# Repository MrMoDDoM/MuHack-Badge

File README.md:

# MuHack-Badge
Official repository for MuHack Badge.

The board features an RP2040 as main microcontroller running micropython.
Its job is to setup and stream data from the Bosh Sensor Hub BHI106B, as well as controlling the LEDs.

```Hardware/``` folder contains the KiCad project

```Software/``` folder contains the BOSS system and the sketch for the ESP32

TODOs:
 - [ ] Connect the interrupt line of BHI to the RP2040
 - [ ] Invert TX/RX of UART between ESP32 and RP2040
 - [ ] Change to a bigger footprint of ESP32 debug port
 - [ ] Maybe add two button for boot sel and reset for the ESP32
 - [ ] Change button battery footprint
 - [ ] Improve silkscreen text size
 - [ ] Add silkscreen label for many things (pinout, battery polarity, etc)
 - [ ] Expose BHI's internal I2C and interrupt line (for future sensors)
 - [ ] Move I2C pull-up resistor
 - [ ] Add led polarity
 - [ ] Remove power inductor (or change to an available one)
 - [ ] Maybe add a way to switch LEDs data line to the ESP32 instead of the RP2040
 - [ ] Docs and code comments
 - [ ] Remove the D16 Schottky Diode from the battery line
 
 Special Thanks to:
 @gcammisa and Paolino

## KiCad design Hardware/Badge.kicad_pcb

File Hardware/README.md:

# MuHack-Badge
Official repository for MuHack Badge

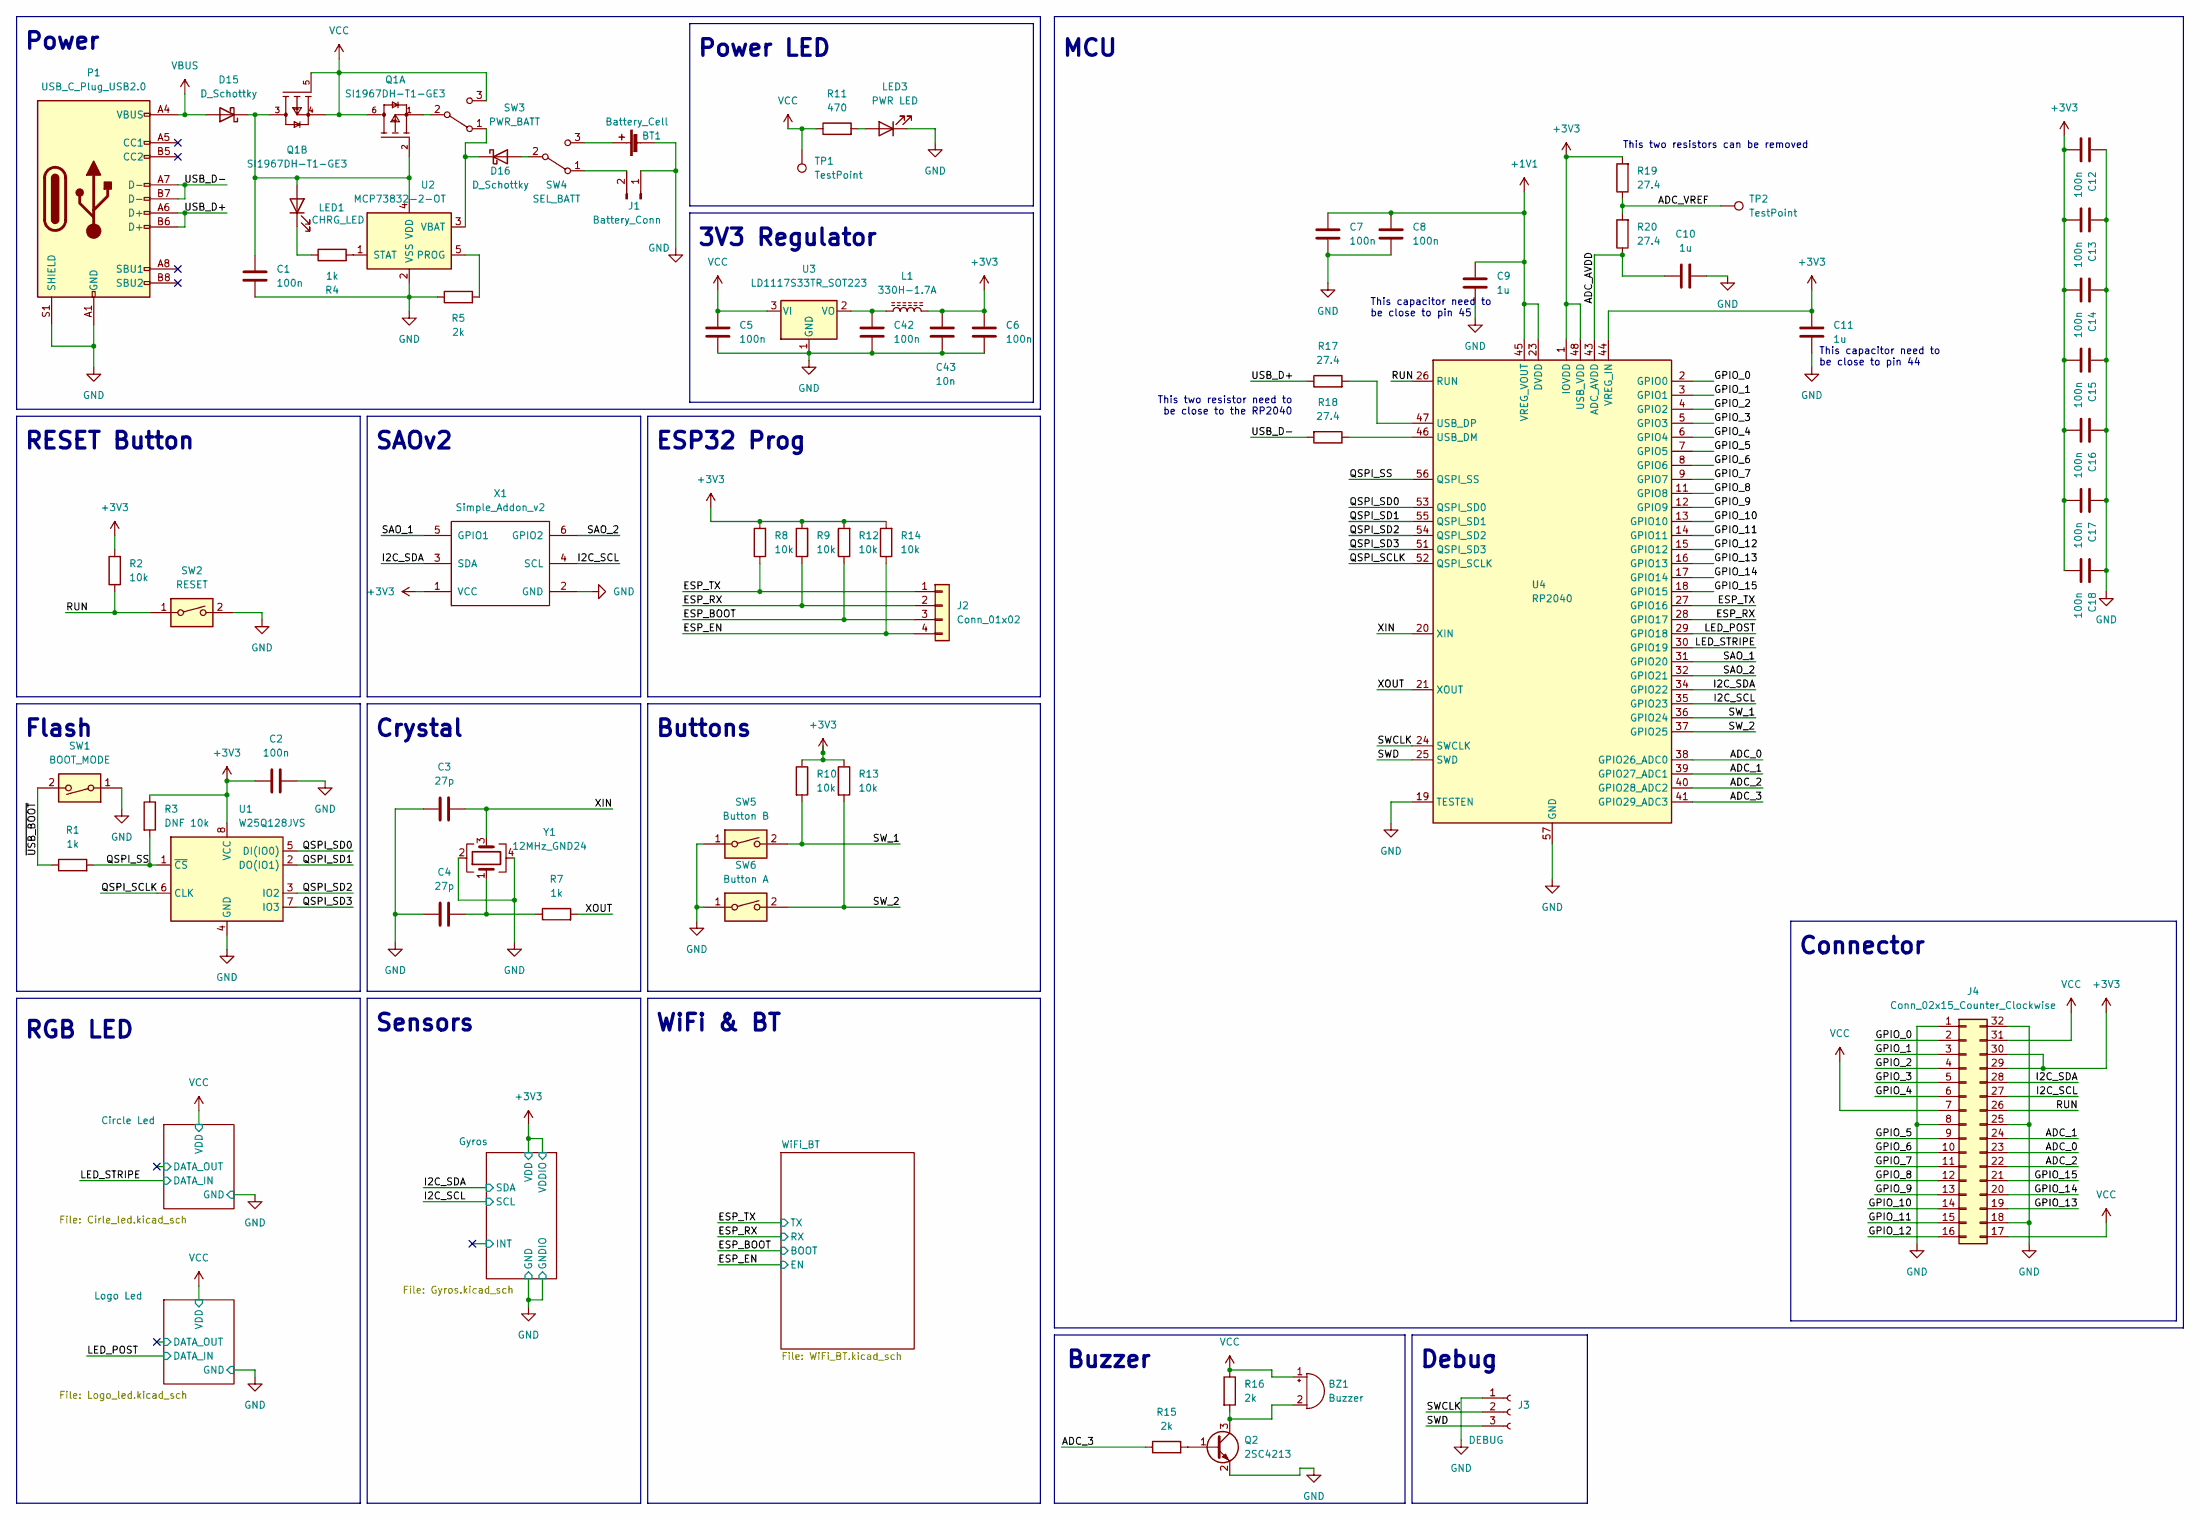
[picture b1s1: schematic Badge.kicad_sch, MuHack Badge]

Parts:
BT1: Battery_Cell; BatteryHolder_LINX_BAT-HLD-012-SMT
BZ1: Buzzer; Buzzer_Mallory_AST1109MLTRQ
C1, C2, C5, C6, C7, C8, C12, C13, C14, C15, C16, C17, C18, C42: 100n; C_0402_1005Metric
C3, C4: 27p; C_0402_1005Metric
C9, C10, C11: 1u; C_0402_1005Metric
C43: 10n; C_0402_1005Metric
D15, D16: D_Schottky; D_SMA
J1: Battery_Conn; JST_PH_B2B-PH-K_1x02_P2.00mm_Vertical
J2: Conn_01x02; PinSocket_1x04_P1.00mm_Vertical
J3: DEBUG; PinSocket_1x03_P2.54mm_Vertical
J4: Conn_02x15_Counter_Clockwise; PinSocket_2x16_P2.54mm_Vertical
L1: 330H-1.7A; L_0603_1608Metric
LED1: CHRG_LED; LED_0603_1608Metric
LED3: PWR LED; LED_0603_1608Metric
P1: USB_C_Plug_USB2.0; USB_C_Receptacle_Palconn_UTC16-G
Q1: SI1967DH-T1-GE3; Vishay-S-03946-07_2001-B-0; mouser part number 781-SI1967DH-T1-GE3; digikey description MOSFET 2P-CH 20V 1.3A SC70-6
Q2: 2SC4213; SOT-323_SC-70
R1, R4, R7: 1k; R_0402_1005Metric
R2, R8, R9, R10, R12, R13, R14: 10k; R_0402_1005Metric
R3: DNF 10k; R_0402_1005Metric
R5, R15, R16: 2k; R_0402_1005Metric
R11: 470; R_0402_1005Metric
R17, R18, R19, R20: 27.4; R_0402_1005Metric
SW1: BOOT_MODE; TS-1187A-B-A-B
SW2: RESET; TS-1187A-B-A-B
SW3: PWR_BATT; SW_SPDT_CK-JS102011SAQN
SW4: SEL_BATT; SW_SPDT_CK-JS102011SAQN
SW5: Button B; TS-1187A-B-A-B
SW6: Button A; TS-1187A-B-A-B
TP1, TP2: TestPoint; TestPoint_Pad_D1.0mm
U1: W25Q128JVS; SOIC-8_5.23x5.23mm_P1.27mm
U2: MCP73832-2-OT; SOT-23-5
U3: LD1117S33TR_SOT223; SOT-223-3_TabPin2
U4: RP2040; QFN-56-1EP_7x7mm_P0.4mm_EP3.2x3.2mm
X1: Simple_Addon_v2; Simple_Addon_v2-BADGE-2x3
Y1: 12MHz_GND24; Crystal_SMD_3225-4Pin_3.2x2.5mm

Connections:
+1V1: C7.1, C8.1, C9.2, U4.23 (DVDD), U4.45 (VREG_VOUT), U4.50 (DVDD)
+3V3: C2.1, C6.2, C11.1, C12.2, C13.2, C14.2, C15.2, C16.2, C17.2, C18.2, C43.2, J4.29, J4.30, L1.2, R2.2, R3.1, R8.2, R9.2, R10.1, R12.2, R13.1, R14.2, R19.2, U1.8 (VCC), U4.1 (IOVDD), U4.10 (IOVDD), U4.22 (IOVDD), U4.33 (IOVDD), U4.42 (IOVDD), U4.44 (VREG_IN), U4.48 (USB_VDD), U4.49 (IOVDD), X1.1 (VCC); also elsewhere on the board
/ADC_0: J4.23, U4.38 (GPIO26_ADC0)
/ADC_1: J4.24, U4.39 (GPIO27_ADC1)
/ADC_2: J4.22, U4.40 (GPIO28_ADC2)
/ADC_3: R15.1, U4.41 (GPIO29_ADC3)
/ADC_AVDD: C10.1, R20.1, U4.43 (ADC_AVDD)
/ADC_VREF: R19.1, R20.2, TP2.1
/ESP_BOOT: J2.3, R12.1; also elsewhere on the board
/ESP_EN: J2.4, R14.1; also elsewhere on the board
/ESP_RX: J2.2, R9.1, U4.28 (GPIO17); also elsewhere on the board
/ESP_TX: J2.1, R8.1, U4.27 (GPIO16); also elsewhere on the board
/GPIO_0: J4.2, U4.2 (GPIO0)
/GPIO_1: J4.3, U4.3 (GPIO1)
/GPIO_2: J4.4, U4.4 (GPIO2)
/GPIO_3: J4.5, U4.5 (GPIO3)
/GPIO_4: J4.6, U4.6 (GPIO4)
/GPIO_5: J4.9, U4.7 (GPIO5)
/GPIO_6: J4.10, U4.8 (GPIO6)
/GPIO_7: J4.11, U4.9 (GPIO7)
/GPIO_8: J4.12, U4.11 (GPIO8)
/GPIO_9: J4.13, U4.12 (GPIO9)
/GPIO_10: J4.14, U4.13 (GPIO10)
/GPIO_11: J4.15, U4.14 (GPIO11)
/GPIO_12: J4.16, U4.15 (GPIO12)
/GPIO_13: J4.19, U4.16 (GPIO13)
/GPIO_14: J4.20, U4.17 (GPIO14)
/GPIO_15: J4.21, U4.18 (GPIO15)
/I2C_SCL: J4.27, U4.35 (GPIO23), X1.4 (SCL); also elsewhere on the board
/I2C_SDA: J4.28, U4.34 (GPIO22), X1.3 (SDA); also elsewhere on the board
/LED_POST: U4.29 (GPIO18); also elsewhere on the board
/LED_STRIPE: U4.30 (GPIO19); also elsewhere on the board
/QSPI_SCLK: U1.6 (CLK), U4.52 (QSPI_SCLK)
/QSPI_SD0: U1.5 (DI(IO0)), U4.53 (QSPI_SD0)
/QSPI_SD1: U1.2 (DO(IO1)), U4.55 (QSPI_SD1)
/QSPI_SD2: U1.3 (IO2), U4.54 (QSPI_SD2)
/QSPI_SD3: U1.7 (IO3), U4.51 (QSPI_SD3)
/QSPI_SS: R1.2, R3.2, U1.1 (~CS), U4.56 (QSPI_SS)
/RUN: J4.26, R2.1, SW2.1, U4.26 (RUN)
/SAO_1: U4.31 (GPIO20), X1.5 (GPIO1)
/SAO_2: U4.32 (GPIO21), X1.6 (GPIO2)
/SWCLK: J3.2, U4.24 (SWCLK)
/SWD: J3.3, U4.25 (SWD)
/SW_1: R10.2, SW5.2, U4.36 (GPIO24)
/SW_2: R13.2, SW6.2, U4.37 (GPIO25)
/USB_D+: P1.A6 (D+), P1.B6 (D+), R17.1
/USB_D-: P1.A7 (D-), P1.B7 (D-), R18.2
/XIN: C3.2, U4.20 (XIN), Y1.3
/XOUT: R7.2, U4.21 (XOUT)
/~USB_BOOT: R1.1, SW1.2
GND: BT1.2 (-), C1.2, C2.2, C3.1, C4.1, C5.1, C6.1, C7.2, C8.2, C9.1, C10.2, C11.2, C12.1, C13.1, C14.1, C15.1, C16.1, C17.1, C18.1, C42.1, C43.1, J1.1, J3.1, J4.1, J4.8, J4.18, J4.25, J4.32, LED3.1 (K), P1.A1 (GND), P1.A12 (GND), P1.B1 (GND), P1.B12 (GND), P1.S1 (SHIELD), Q2.2 (E), R5.1, SW1.1, SW2.2, SW5.1, SW6.1, U1.4 (GND), U2.2 (VSS), U3.1 (GND), U4.19 (TESTEN), U4.57 (GND), X1.2 (GND), Y1.2, Y1.4; also elsewhere on the board
unnamed: BT1.1 (+), SW4.3 (C)
unnamed: BZ1.2 (+), Q2.3 (C), R16.2
unnamed: C1.1, D15.1 (K), LED1.2 (A), Q1.2 (G1), Q1.3 (D2), U2.4 (VDD)
unnamed: C4.2, R7.1, Y1.1
unnamed: C42.2, L1.1, U3.2 (VO)
unnamed: D16.1 (K), SW3.1 (A), U2.3 (VBAT)
unnamed: D16.2 (A), SW4.2 (B)
unnamed: J1.2, SW4.1 (A)
unnamed: LED1.1 (K), R4.1
unnamed: LED3.2 (A), R11.2
unnamed: Q1.1 (S1), SW3.2 (B)
unnamed: Q2.1 (B), R15.2
unnamed: R4.2, U2.1 (STAT)
unnamed: R5.2, U2.5 (PROG)
unnamed: R17.2, U4.47 (USB_DP)
unnamed: R18.1, U4.46 (USB_DM)
VBUS: D15.2 (A), P1.A4 (VBUS), P1.A9 (VBUS), P1.B4 (VBUS), P1.B9 (VBUS)
VCC: BZ1.1 (-), C5.2, J4.7, J4.17, J4.31, Q1.4 (S2), Q1.5 (G2), Q1.6 (D1), R11.1, R16.1, SW3.3 (C), TP1.1, U3.3 (VI); also elsewhere on the board

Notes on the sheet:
This capacitor need to be close to pin 44
Buttons
Power
This two resistor need to be close to the RP2040
ESP32 Prog
3V3 Regulator
Crystal
Power LED
This capacitor need to be close to pin 45
RESET Button
This two resistors can be removed
WiFi & BT
Connector
SAOv2
Buzzer
Flash
Debug
Sensors
MCU
RGB LED

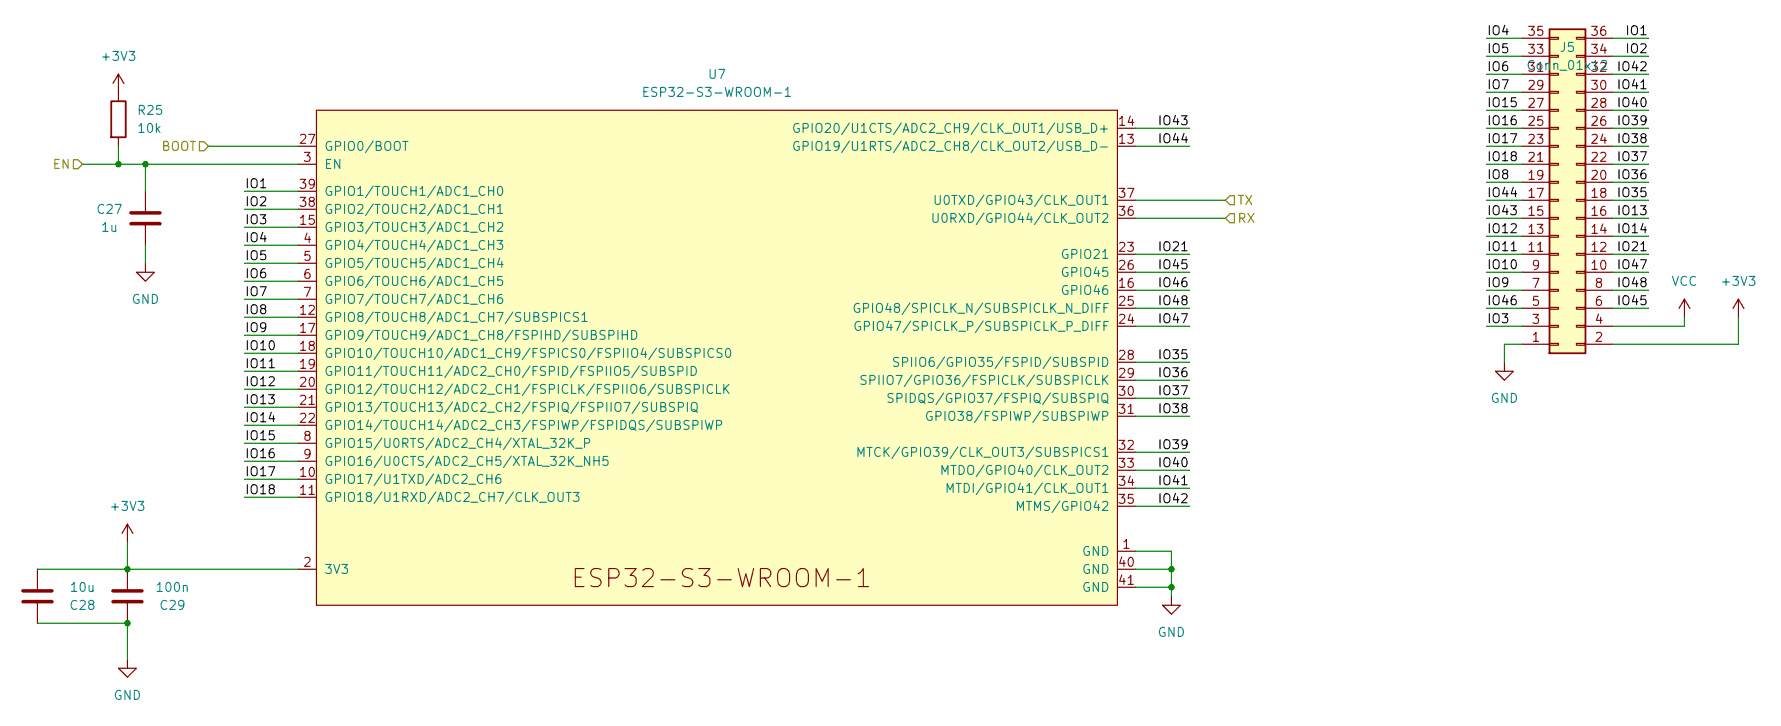
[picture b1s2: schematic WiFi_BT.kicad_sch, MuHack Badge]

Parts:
C27: 1u; C_0402_1005Metric
C28: 10u; C_0402_1005Metric
C29: 100n; C_0402_1005Metric
J5: Conn_01x12; PinSocket_2x18_P1.27mm_Vertical
R25: 10k; R_0402_1005Metric
U7: ESP32-S3-WROOM-1

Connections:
+3V3: C28.1, C29.1, J5.2, R25.1, U7.2 (3V3); also elsewhere on the board
/ESP_BOOT: U7.27 (GPIO0/BOOT); also elsewhere on the board
/ESP_EN: C27.2, R25.2, U7.3 (EN); also elsewhere on the board
/ESP_RX: U7.36 (U0RXD/GPIO44/CLK_OUT2); also elsewhere on the board
/ESP_TX: U7.37 (U0TXD/GPIO43/CLK_OUT1); also elsewhere on the board
/WiFi_BT/IO1: J5.36, U7.39 (GPIO1/TOUCH1/ADC1_CH0)
/WiFi_BT/IO2: J5.34, U7.38 (GPIO2/TOUCH2/ADC1_CH1)
/WiFi_BT/IO3: J5.3, U7.15 (GPIO3/TOUCH3/ADC1_CH2)
/WiFi_BT/IO4: J5.35, U7.4 (GPIO4/TOUCH4/ADC1_CH3)
/WiFi_BT/IO5: J5.33, U7.5 (GPIO5/TOUCH5/ADC1_CH4)
/WiFi_BT/IO6: J5.31, U7.6 (GPIO6/TOUCH6/ADC1_CH5)
/WiFi_BT/IO7: J5.29, U7.7 (GPIO7/TOUCH7/ADC1_CH6)
/WiFi_BT/IO8: J5.19, U7.12 (GPIO8/TOUCH8/ADC1_CH7/SUBSPICS1)
/WiFi_BT/IO9: J5.7, U7.17 (GPIO9/TOUCH9/ADC1_CH8/FSPIHD/SUBSPIHD)
/WiFi_BT/IO10: J5.9, U7.18 (GPIO10/TOUCH10/ADC1_CH9/FSPICS0/FSPIIO4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)
/WiFi_BT/IO11: J5.11, U7.19 (GPIO11/TOUCH11/ADC2_CH0/FSPID/FSPIIO5/S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)
/WiFi_BT/IO12: J5.13, U7.20 (GPIO12/TOUCH12/ADC2_CH1/FSPICLK/FSPIIO6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)
/WiFi_BT/IO13: J5.16, U7.21 (GPIO13/TOUCH13/ADC2_CH2/FSPIQ/FSPIIO7/S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)
/WiFi_BT/IO14: J5.14, U7.22 (GPIO14/TOUCH14/ADC2_CH3/FSPIWP/FSPIDQS/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)
/WiFi_BT/IO15: J5.27, U7.8 (GPIO15/U0RTS/ADC2_CH4/XTAL_32K_P)
/WiFi_BT/IO16: J5.25, U7.9 (GPIO16/U0CTS/ADC2_CH5/XTAL_32K_NH5)
/WiFi_BT/IO17: J5.23, U7.10 (GPIO17/U1TXD/ADC2_CH6)
/WiFi_BT/IO18: J5.21, U7.11 (GPIO18/U1RXD/ADC2_CH7/CLK_OUT3)
/WiFi_BT/IO21: J5.12, U7.23 (GPIO21)
/WiFi_BT/IO35: J5.18, U7.28 (SPIIO6/GPIO35/FSPID/SUBSPID)
/WiFi_BT/IO36: J5.20, U7.29 (SPIIO7/GPIO36/FSPICLK/SUBSPICLK)
/WiFi_BT/IO37: J5.22, U7.30 (SPIDQS/GPIO37/FSPIQ/SUBSPIQ)
/WiFi_BT/IO38: J5.24, U7.31 (GPIO38/FSPIWP/SUBSPIWP)
/WiFi_BT/IO39: J5.26, U7.32 (MTCK/GPIO39/CLK_OUT3/SUBSPICS1)
/WiFi_BT/IO40: J5.28, U7.33 (MTDO/GPIO40/CLK_OUT2)
/WiFi_BT/IO41: J5.30, U7.34 (MTDI/GPIO41/CLK_OUT1)
/WiFi_BT/IO42: J5.32, U7.35 (MTMS/GPIO42)
/WiFi_BT/IO43: J5.15, U7.14 (GPIO20/U1CTS/ADC2_CH9/CLK_OUT1/USB_D+)
/WiFi_BT/IO44: J5.17, U7.13 (GPIO19/U1RTS/ADC2_CH8/CLK_OUT2/USB_D-)
/WiFi_BT/IO45: J5.6, U7.26 (GPIO45)
/WiFi_BT/IO46: J5.5, U7.16 (GPIO46)
/WiFi_BT/IO47: J5.10, U7.24 (GPIO47/SPICLK_P/SUBSPICLK_P_DIFF)
/WiFi_BT/IO48: J5.8, U7.25 (GPIO48/SPICLK_N/SUBSPICLK_N_DIFF)
GND: C27.1, C28.2, C29.2, J5.1, U7.1 (GND), U7.40 (GND), U7.41 (GND); also elsewhere on the board
VCC: J5.4; also elsewhere on the board

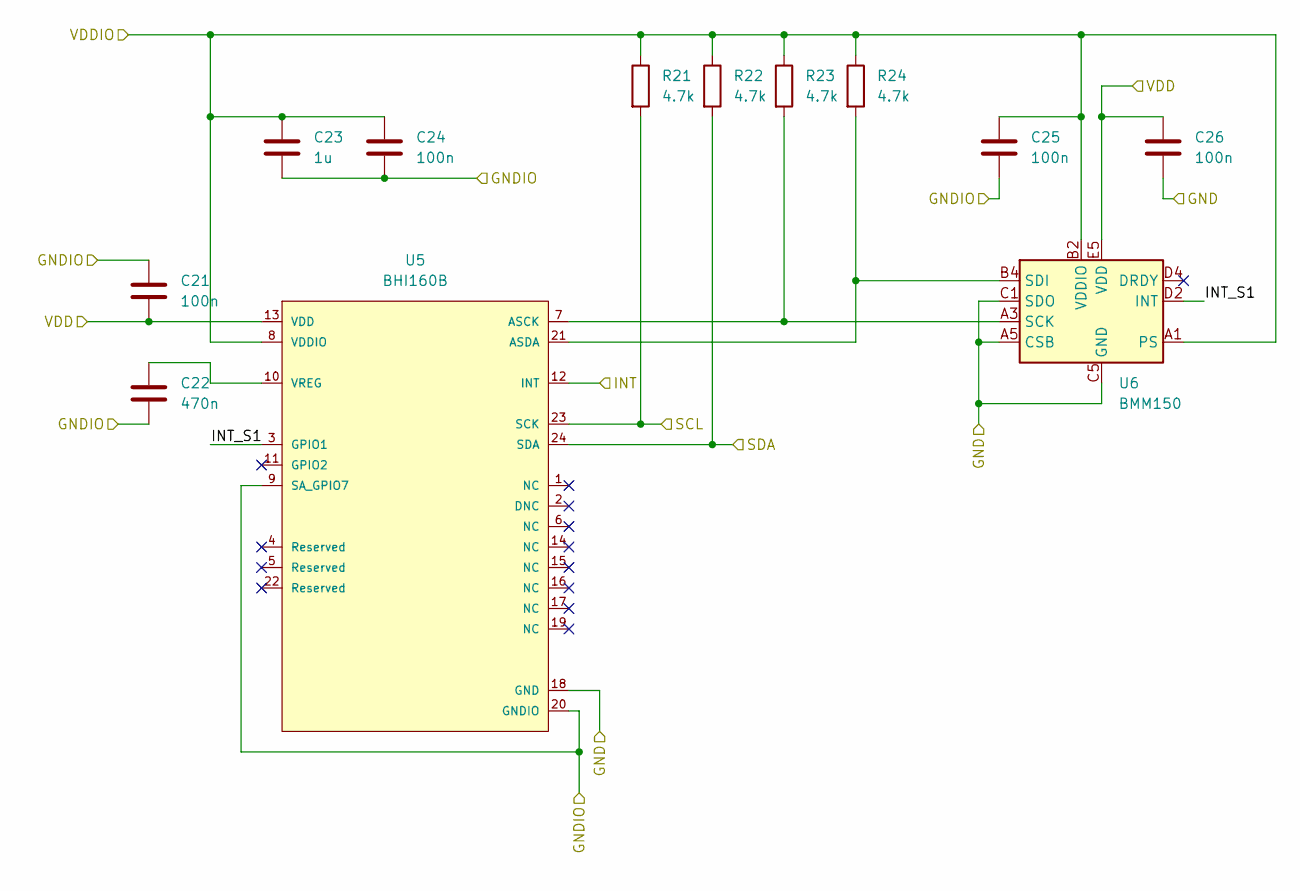
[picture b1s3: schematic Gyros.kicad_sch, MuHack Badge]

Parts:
C21, C24, C25, C26: 100n; C_0402_1005Metric
C22: 470n; C_0402_1005Metric
C23: 1u; C_0402_1005Metric
R21, R22, R23, R24: 4.7k; R_0402_1005Metric
U5: BHI160B; Bosch_Sensortec-BHI160B-MFG; mouser part number 262-BHI160B; digikey description IMU ACCEL/GYRO 3-AXIS I2C 24LGA
U6: BMM150; Bosch_Sensortec-BMM150-IPC_B

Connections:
+3V3: C21.2, C23.1, C24.1, C25.2, C26.2, R21.1, R22.1, R23.1, R24.1, U5.8 (VDDIO), U5.13 (VDD), U6.A1 (PS), U6.B2 (VDDIO), U6.E5 (VDD); also elsewhere on the board
/Gyros/INT: U5.12 (INT)
/Gyros/INT_S1: U5.3 (GPIO1), U6.D2 (INT)
/I2C_SCL: R21.2, U5.23 (SCK); also elsewhere on the board
/I2C_SDA: R22.2, U5.24 (SDA); also elsewhere on the board
GND: C21.1, C22.2, C23.2, C24.2, C25.1, C26.1, U5.9 (SA_GPIO7), U5.18 (GND), U5.20 (GNDIO), U6.A5 (CSB), U6.C1 (SDO), U6.C5 (GND), U6.E1 (GND), U6.E3 (GND); also elsewhere on the board
unnamed: C22.1, U5.10 (VREG)
unnamed: R23.2, U5.7 (ASCK), U6.A3 (SCK)
unnamed: R24.2, U5.21 (ASDA), U6.B4 (SDI)

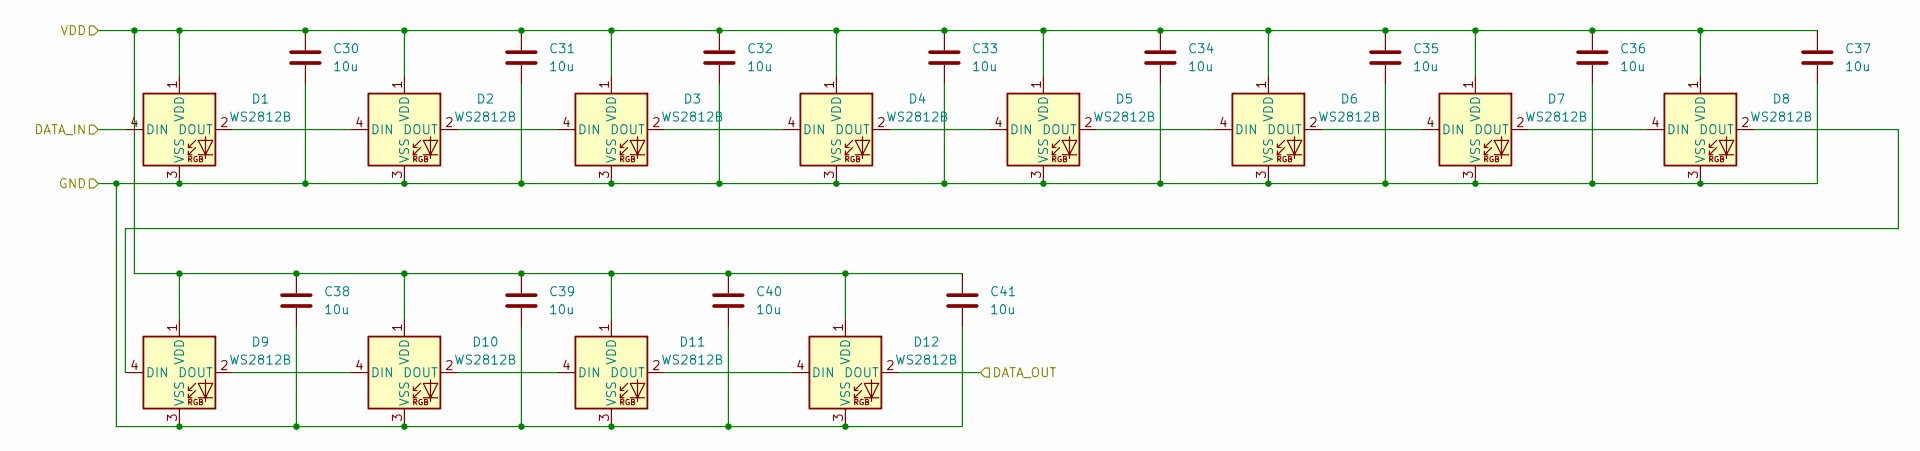
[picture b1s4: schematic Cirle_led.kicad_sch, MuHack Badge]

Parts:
C30, C31, C32, C33, C34, C35, C36, C37, C38, C39, C40, C41: 10u; C_0402_1005Metric
D1, D2, D3, D4, D5, D6, D7, D8, D9, D10, D11, D12: WS2812B; LED_WS2812B_PLCC4_5.0x5.0mm_P3.2mm

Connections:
/Circle Led/DATA_OUT: D12.2 (DOUT)
/LED_STRIPE: D1.4 (DIN); also elsewhere on the board
GND: C30.2, C31.2, C32.2, C33.2, C34.2, C35.2, C36.2, C37.2, C38.2, C39.2, C40.2, C41.2, D1.3 (VSS), D2.3 (VSS), D3.3 (VSS), D4.3 (VSS), D5.3 (VSS), D6.3 (VSS), D7.3 (VSS), D8.3 (VSS), D9.3 (VSS), D10.3 (VSS), D11.3 (VSS), D12.3 (VSS); also elsewhere on the board
unnamed: D1.2 (DOUT), D2.4 (DIN)
unnamed: D2.2 (DOUT), D3.4 (DIN)
unnamed: D3.2 (DOUT), D4.4 (DIN)
unnamed: D4.2 (DOUT), D5.4 (DIN)
unnamed: D5.2 (DOUT), D6.4 (DIN)
unnamed: D6.2 (DOUT), D7.4 (DIN)
unnamed: D7.2 (DOUT), D8.4 (DIN)
unnamed: D8.2 (DOUT), D9.4 (DIN)
unnamed: D10.2 (DOUT), D11.4 (DIN)
unnamed: D9.2 (DOUT), D10.4 (DIN)
unnamed: D11.2 (DOUT), D12.4 (DIN)
VCC: C30.1, C31.1, C32.1, C33.1, C34.1, C35.1, C36.1, C37.1, C38.1, C39.1, C40.1, C41.1, D1.1 (VDD), D2.1 (VDD), D3.1 (VDD), D4.1 (VDD), D5.1 (VDD), D6.1 (VDD), D7.1 (VDD), D8.1 (VDD), D9.1 (VDD), D10.1 (VDD), D11.1 (VDD), D12.1 (VDD); also elsewhere on the board

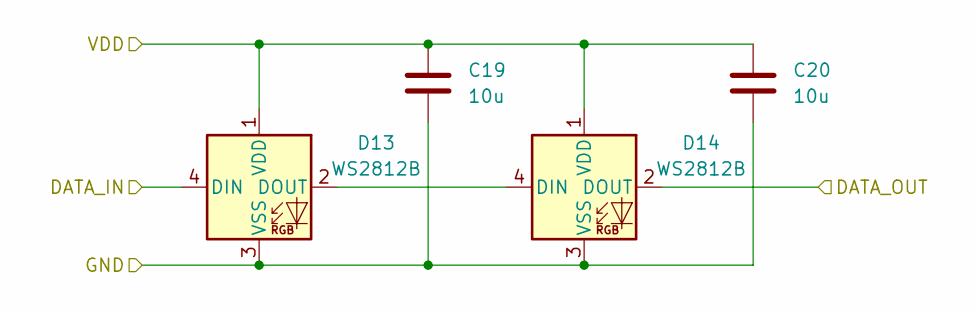
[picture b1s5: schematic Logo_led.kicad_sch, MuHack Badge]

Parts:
C19, C20: 10u; C_0402_1005Metric
D13, D14: WS2812B; LED_WS2812B_PLCC4_5.0x5.0mm_P3.2mm

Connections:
/LED_POST: D13.4 (DIN); also elsewhere on the board
/Logo Led/DATA_OUT: D14.2 (DOUT)
GND: C19.2, C20.2, D13.3 (VSS), D14.3 (VSS); also elsewhere on the board
unnamed: D13.2 (DOUT), D14.4 (DIN)
VCC: C19.1, C20.1, D13.1 (VDD), D14.1 (VDD); also elsewhere on the board

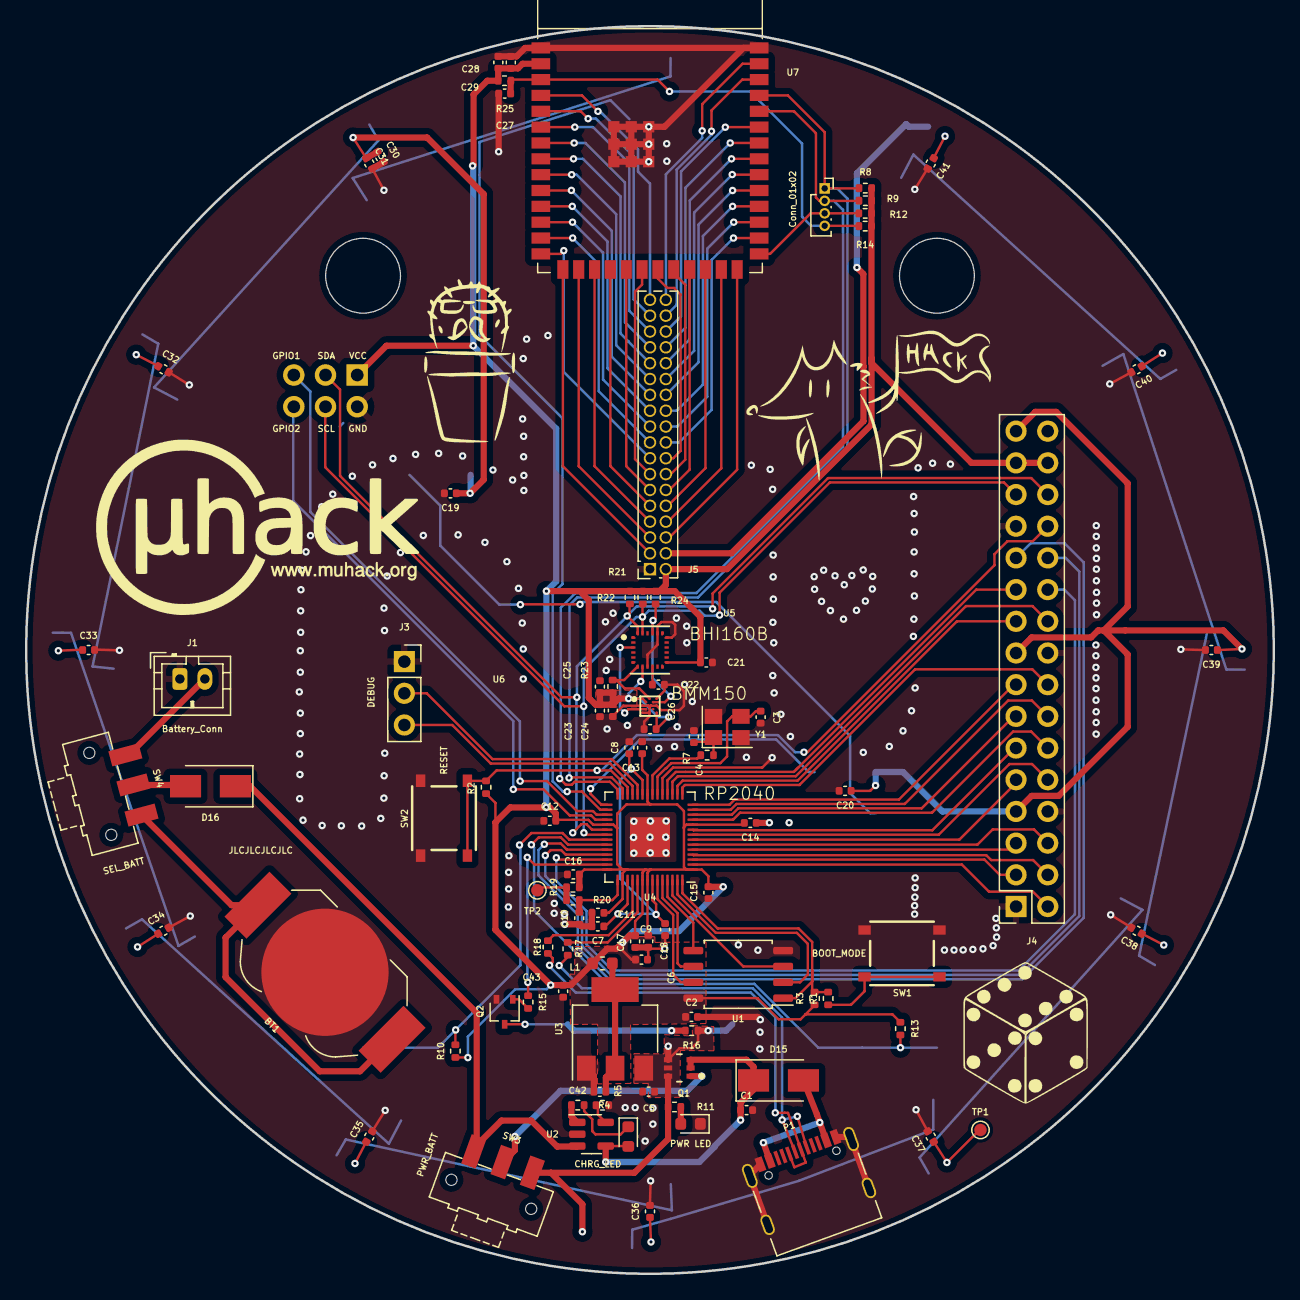
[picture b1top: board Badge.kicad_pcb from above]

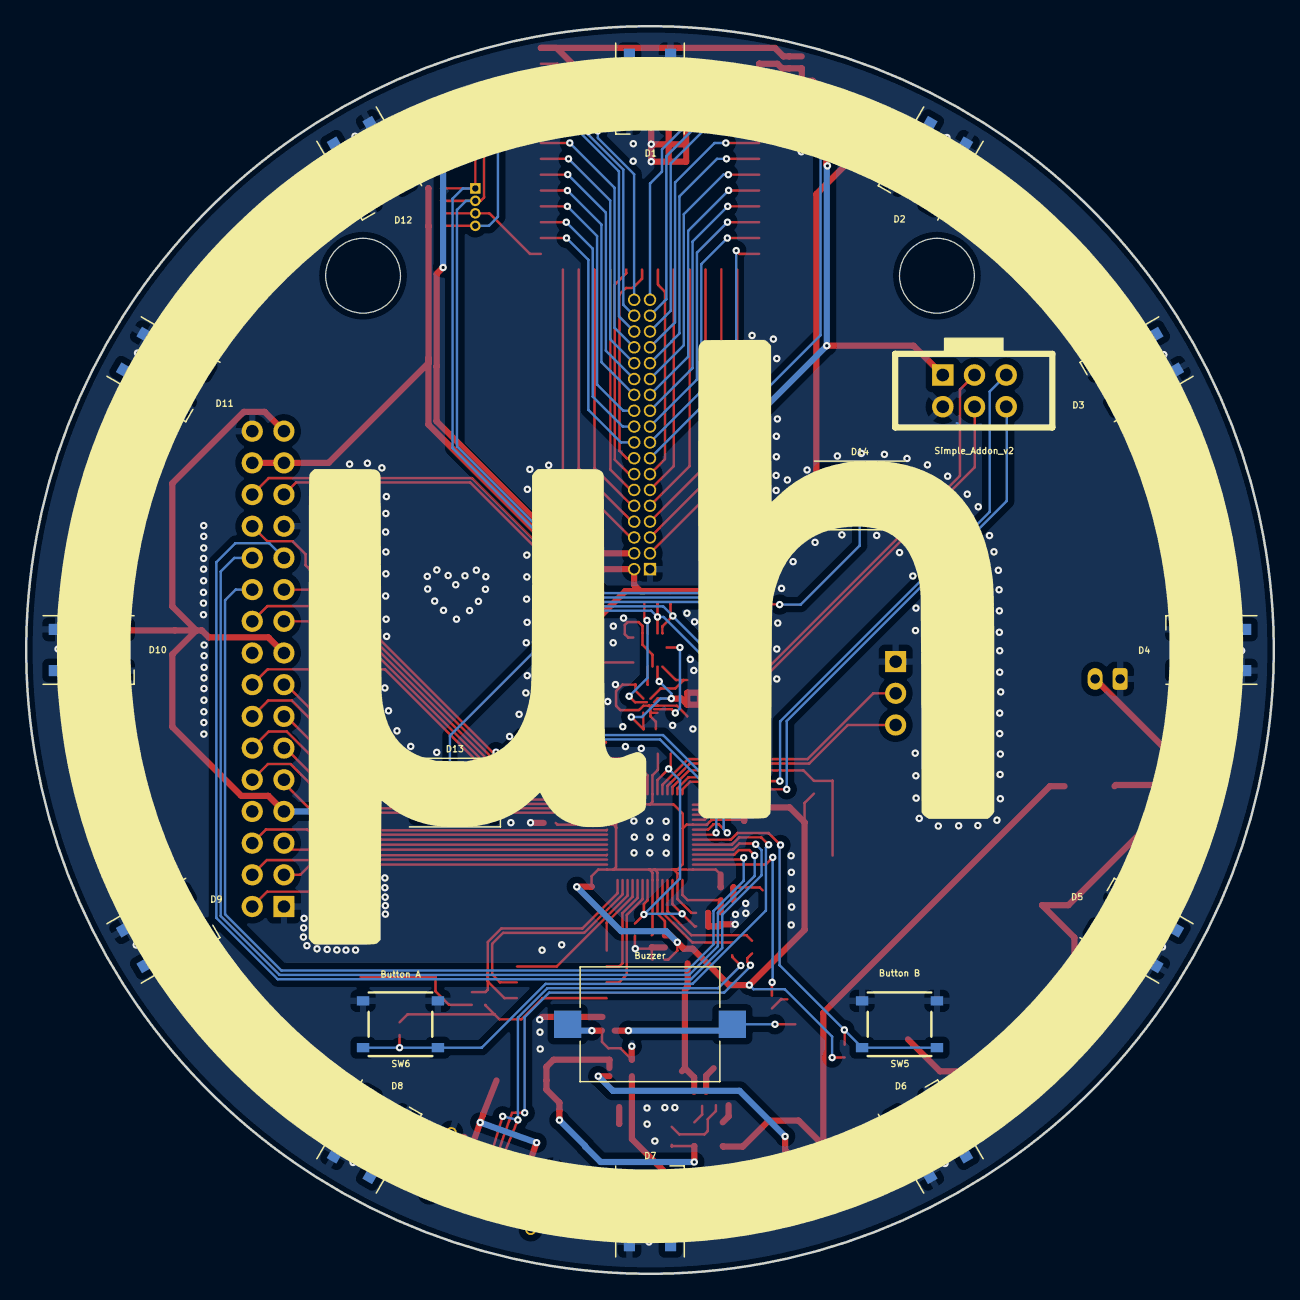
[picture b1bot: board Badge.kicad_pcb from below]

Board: 2 copper layers, 100.0 x 100.0 mm, 113 parts (18 on the bottom side), 118 nets.

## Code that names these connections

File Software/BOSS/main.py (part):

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
applications = []

ESP_TX_PIN = 0
ESP_RX_PIN = 1

LED_LETTER_PIN = 18
LED_LETTER_LEN = 2

LED_STRIPE_PIN = 19
LED_STRIPE_LEN = 12

BUZZER_PIN = 29
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button_B = machine.Pin(BUTTON_B_PIN, Pin.IN)

bhy = BHY(sda=SDA_PIN, scl=SCL_PIN, address=BHY_I2C_ADDR, stand_alone=False, debug=False)
cled = CLED(LED_STRIPE_PIN, LED_STRIPE_LEN, LED_LETTER_PIN, LED_LETTER_LEN, debug=False)

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sensor_config = []
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remapping_matrix = [1,0,0,0,1,0,0,0,-1] # P? ? - obtained from experimenting with the accelerometer

def testHardware():
    led_stripe = neopixel.NeoPixel(machine.Pin(LED_STRIPE_PIN), LED_STRIPE_LEN)
    led_letter = neopixel.NeoPixel(machine.Pin(LED_LETTER_PIN), LED_LETTER_LEN)
    try:
        print("Testing LED Stripe")
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
def UARTPassThrough():
    try:
        esp_uart = machine.UART(0, 115200, tx=Pin(ESP_TX_PIN), rx=Pin(ESP_RX_PIN))

        sys_uart_thread = _thread.start_new_thread(from_stdin_to_uart, (esp_uart,1))
        while True:
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
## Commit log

2022-10-26 First Commit - version 1.0
2022-10-27 Added SAOv2 Connector - re-arranged some RP pins connection
2022-10-27 Connected both USB-C data signal, moved the crystal - revisisted ready for production
2022-11-24 First BOSS commit, added BasicOTA (not working), updated Hardware .gitignore
2022-11-24 Update READMEs
2022-11-25 Change License
2022-11-25 Improved the headless mode, CLED system and minor bug fix - UNSATBLE
2022-11-25 Headless mode is working, added idle animation - there are still some bugs with CLED
2022-11-29 Added drawVector and Linear Acceleration app
2022-11-29 Updated TODOs and re-enabled startup sound
